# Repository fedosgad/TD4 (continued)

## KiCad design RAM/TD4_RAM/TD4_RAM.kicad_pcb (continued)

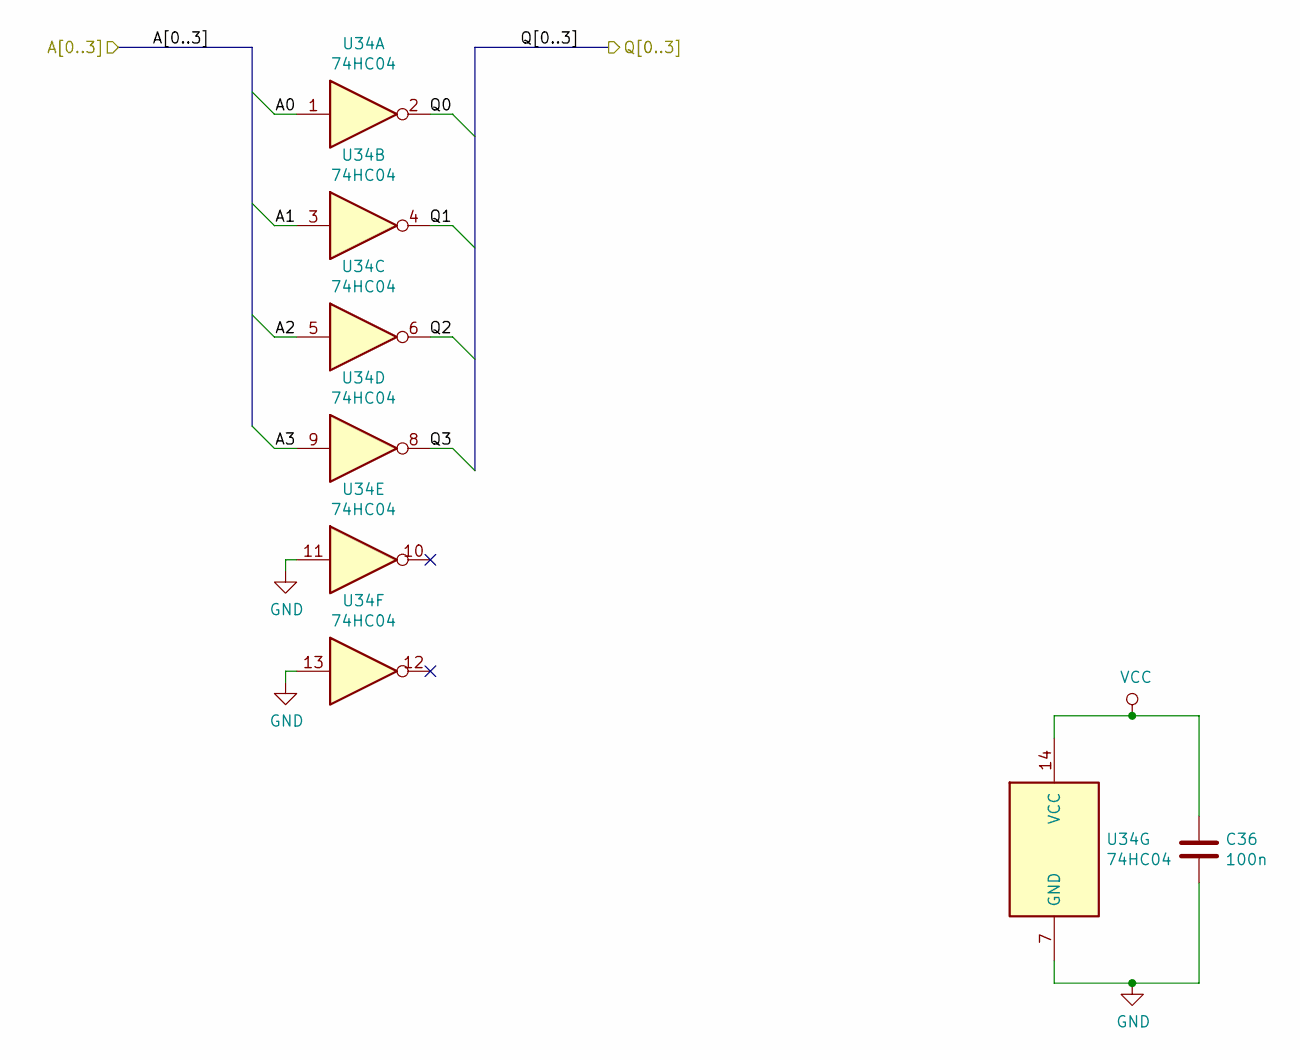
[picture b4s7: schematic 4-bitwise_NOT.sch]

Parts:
C5: 100n; C_0805_2012Metric
U3: 74HC04; SOIC-14_3.9x8.7mm_P1.27mm

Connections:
/Address comparator/2x Quad AND/A0: U3.2; also elsewhere on the board
/Address comparator/2x Quad AND/A1: U3.4; also elsewhere on the board
/Address comparator/2x Quad AND/A2: U3.6; also elsewhere on the board
/Address comparator/2x Quad AND/A3: U3.8; also elsewhere on the board
/Address comparator/4-bitwise NOT/A0: U3.1; also elsewhere on the board
/Address comparator/4-bitwise NOT/A1: U3.3; also elsewhere on the board
/Address comparator/4-bitwise NOT/A2: U3.5; also elsewhere on the board
/Address comparator/4-bitwise NOT/A3: U3.9; also elsewhere on the board
VCC: C5.1, U3.14 (VCC); also elsewhere on the board

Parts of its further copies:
C22, C23, C24, C25, C26, C27, C28, C29, C30, C31, C32, C33, C34, C35, C36: 100n; C_0805_2012Metric
U20, U21, U22, U23, U24, U25, U26, U27, U28, U29, U30, U31, U32, U33, U34: 74HC04; SOIC-14_3.9x8.7mm_P1.27mm

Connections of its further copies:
/Address comparator/2x Quad AND/B0: U20.2; also elsewhere on the board
/Address comparator/2x Quad AND/B1: U20.4; also elsewhere on the board
/Address comparator/2x Quad AND/B2: U20.6; also elsewhere on the board
/Address comparator/2x Quad AND/B3: U20.8; also elsewhere on the board
/Address comparator/sheet5CCFCFC3/A0: U20.1; also elsewhere on the board
/Address comparator/sheet5CCFCFC3/A1: U20.3; also elsewhere on the board
/Address comparator/sheet5CCFCFC3/A2: U20.5; also elsewhere on the board
/Address comparator/sheet5CCFCFC3/A3: U20.9; also elsewhere on the board
/Address comparator/sheet5CD0A991/A0: U22.1; also elsewhere on the board
/Address comparator/sheet5CD0A991/A1: U22.3; also elsewhere on the board
/Address comparator/sheet5CD0A991/A2: U22.5; also elsewhere on the board
/Address comparator/sheet5CD0A991/A3: U22.9; also elsewhere on the board
/Address comparator/sheet5CD1F070/A0: U31.1; also elsewhere on the board
/Address comparator/sheet5CD1F070/A1: U31.3; also elsewhere on the board
/Address comparator/sheet5CD1F070/A2: U31.5; also elsewhere on the board
/Address comparator/sheet5CD1F070/A3: U31.9; also elsewhere on the board
/Address comparator/sheet5CD1F071/A0: U32.1; also elsewhere on the board
/Address comparator/sheet5CD1F071/A1: U32.3; also elsewhere on the board
/Address comparator/sheet5CD1F071/A2: U32.5; also elsewhere on the board
/Address comparator/sheet5CD1F071/A3: U32.9; also elsewhere on the board
/Address comparator/sheet5CD1F072/A0: U33.1; also elsewhere on the board
/Address comparator/sheet5CD1F072/A1: U33.3; also elsewhere on the board
/Address comparator/sheet5CD1F072/A2: U33.5; also elsewhere on the board
/Address comparator/sheet5CD1F072/A3: U33.9; also elsewhere on the board
/Address comparator/sheet5CD1F073/A0: U34.1; also elsewhere on the board
/Address comparator/sheet5CD1F073/A1: U34.3; also elsewhere on the board
/Address comparator/sheet5CD1F073/A2: U34.5; also elsewhere on the board
/Address comparator/sheet5CD1F073/A3: U34.9; also elsewhere on the board
/Address comparator/sheet5CD2F160/A0: U23.2; also elsewhere on the board
/Address comparator/sheet5CD2F160/A1: U23.4; also elsewhere on the board
/Address comparator/sheet5CD2F160/A2: U23.6; also elsewhere on the board
/Address comparator/sheet5CD2F160/A3: U23.8; also elsewhere on the board
/Address comparator/sheet5CD2F160/B0: U24.2; also elsewhere on the board
/Address comparator/sheet5CD2F160/B1: U24.4; also elsewhere on the board
/Address comparator/sheet5CD2F160/B2: U24.6; also elsewhere on the board
/Address comparator/sheet5CD2F160/B3: U24.8; also elsewhere on the board
/Address comparator/sheet5CD03CAA/A0: U21.1; also elsewhere on the board
/Address comparator/sheet5CD03CAA/A1: U21.3; also elsewhere on the board
/Address comparator/sheet5CD03CAA/A2: U21.5; also elsewhere on the board
/Address comparator/sheet5CD03CAA/A3: U21.9; also elsewhere on the board
/Address comparator/sheet5CD3CB46/A0: U27.2; also elsewhere on the board
/Address comparator/sheet5CD3CB46/A1: U27.4; also elsewhere on the board
/Address comparator/sheet5CD3CB46/A2: U27.6; also elsewhere on the board
/Address comparator/sheet5CD3CB46/A3: U27.8; also elsewhere on the board
/Address comparator/sheet5CD3CB46/B0: U28.2; also elsewhere on the board
/Address comparator/sheet5CD3CB46/B1: U28.4; also elsewhere on the board
/Address comparator/sheet5CD3CB46/B2: U28.6; also elsewhere on the board
/Address comparator/sheet5CD3CB46/B3: U28.8; also elsewhere on the board
/Address comparator/sheet5CD3CB47/A0: U29.2; also elsewhere on the board
/Address comparator/sheet5CD3CB47/A1: U29.4; also elsewhere on the board
/Address comparator/sheet5CD3CB47/A2: U29.6; also elsewhere on the board
/Address comparator/sheet5CD3CB47/A3: U29.8; also elsewhere on the board
/Address comparator/sheet5CD3CB47/B0: U30.2; also elsewhere on the board
/Address comparator/sheet5CD3CB47/B1: U30.4; also elsewhere on the board
/Address comparator/sheet5CD3CB47/B2: U30.6; also elsewhere on the board
/Address comparator/sheet5CD3CB47/B3: U30.8; also elsewhere on the board
/Address comparator/sheet5CD3CB48/A0: U31.2; also elsewhere on the board
/Address comparator/sheet5CD3CB48/A1: U31.4; also elsewhere on the board
/Address comparator/sheet5CD3CB48/A2: U31.6; also elsewhere on the board
/Address comparator/sheet5CD3CB48/A3: U31.8; also elsewhere on the board
/Address comparator/sheet5CD3CB48/B0: U32.2; also elsewhere on the board
/Address comparator/sheet5CD3CB48/B1: U32.4; also elsewhere on the board
/Address comparator/sheet5CD3CB48/B2: U32.6; also elsewhere on the board
/Address comparator/sheet5CD3CB48/B3: U32.8; also elsewhere on the board
/Address comparator/sheet5CD3CB49/A0: U33.2; also elsewhere on the board
/Address comparator/sheet5CD3CB49/A1: U33.4; also elsewhere on the board
/Address comparator/sheet5CD3CB49/A2: U33.6; also elsewhere on the board
/Address comparator/sheet5CD3CB49/A3: U33.8; also elsewhere on the board
/Address comparator/sheet5CD3CB49/B0: U34.2; also elsewhere on the board
/Address comparator/sheet5CD3CB49/B1: U34.4; also elsewhere on the board
/Address comparator/sheet5CD3CB49/B2: U34.6; also elsewhere on the board
/Address comparator/sheet5CD3CB49/B3: U34.8; also elsewhere on the board
/Address comparator/sheet5CD35E49/A0: U25.2; also elsewhere on the board
/Address comparator/sheet5CD35E49/A1: U25.4; also elsewhere on the board
/Address comparator/sheet5CD35E49/A2: U25.6; also elsewhere on the board
/Address comparator/sheet5CD35E49/A3: U25.8; also elsewhere on the board
/Address comparator/sheet5CD35E49/B0: U26.2; also elsewhere on the board
/Address comparator/sheet5CD35E49/B1: U26.4; also elsewhere on the board
/Address comparator/sheet5CD35E49/B2: U26.6; also elsewhere on the board
/Address comparator/sheet5CD35E49/B3: U26.8; also elsewhere on the board
/Address comparator/sheet5CD1837A/A0: U27.1; also elsewhere on the board
/Address comparator/sheet5CD1837A/A1: U27.3; also elsewhere on the board
/Address comparator/sheet5CD1837A/A2: U27.5; also elsewhere on the board
/Address comparator/sheet5CD1837A/A3: U27.9; also elsewhere on the board
/Address comparator/sheet5CD1837B/A0: U28.1; also elsewhere on the board
/Address comparator/sheet5CD1837B/A1: U28.3; also elsewhere on the board
/Address comparator/sheet5CD1837B/A2: U28.5; also elsewhere on the board
/Address comparator/sheet5CD1837B/A3: U28.9; also elsewhere on the board
/Address comparator/sheet5CD1837C/A0: U29.1; also elsewhere on the board
/Address comparator/sheet5CD1837C/A1: U29.3; also elsewhere on the board
/Address comparator/sheet5CD1837C/A2: U29.5; also elsewhere on the board
/Address comparator/sheet5CD1837C/A3: U29.9; also elsewhere on the board
/Address comparator/sheet5CD1837D/A0: U30.1; also elsewhere on the board
/Address comparator/sheet5CD1837D/A1: U30.3; also elsewhere on the board
/Address comparator/sheet5CD1837D/A2: U30.5; also elsewhere on the board
/Address comparator/sheet5CD1837D/A3: U30.9; also elsewhere on the board
/Address comparator/sheet5CD11684/A0: U23.1; also elsewhere on the board
/Address comparator/sheet5CD11684/A1: U23.3; also elsewhere on the board
/Address comparator/sheet5CD11684/A2: U23.5; also elsewhere on the board
/Address comparator/sheet5CD11684/A3: U23.9; also elsewhere on the board
/Address comparator/sheet5CD11685/A0: U24.1; also elsewhere on the board
/Address comparator/sheet5CD11685/A1: U24.3; also elsewhere on the board
/Address comparator/sheet5CD11685/A2: U24.5; also elsewhere on the board
/Address comparator/sheet5CD11685/A3: U24.9; also elsewhere on the board
/Address comparator/sheet5CD11686/A0: U25.1; also elsewhere on the board
/Address comparator/sheet5CD11686/A1: U25.3; also elsewhere on the board
/Address comparator/sheet5CD11686/A2: U25.5; also elsewhere on the board
/Address comparator/sheet5CD11686/A3: U25.9; also elsewhere on the board
/Address comparator/sheet5CD11687/A0: U26.1; also elsewhere on the board
/Address comparator/sheet5CD11687/A1: U26.3; also elsewhere on the board
/Address comparator/sheet5CD11687/A2: U26.5; also elsewhere on the board
/Address comparator/sheet5CD11687/A3: U26.9; also elsewhere on the board
/Address comparator/sheet5CD28477/A0: U21.2; also elsewhere on the board
/Address comparator/sheet5CD28477/A1: U21.4; also elsewhere on the board
/Address comparator/sheet5CD28477/A2: U21.6; also elsewhere on the board
/Address comparator/sheet5CD28477/A3: U21.8; also elsewhere on the board
/Address comparator/sheet5CD28477/B0: U22.2; also elsewhere on the board
/Address comparator/sheet5CD28477/B1: U22.4; also elsewhere on the board
/Address comparator/sheet5CD28477/B2: U22.6; also elsewhere on the board
/Address comparator/sheet5CD28477/B3: U22.8; also elsewhere on the board
VCC: C22.1, C23.1, C24.1, C25.1, C26.1, C27.1, C28.1, C29.1, C30.1, C31.1, C32.1, C33.1, C34.1, C35.1, C36.1, U20.14 (VCC), U21.14 (VCC), U22.14 (VCC), U23.14 (VCC), U24.14 (VCC), U25.14 (VCC), U26.14 (VCC), U27.14 (VCC), U28.14 (VCC), U29.14 (VCC), U30.14 (VCC), U31.14 (VCC), U32.14 (VCC), U33.14 (VCC), U34.14 (VCC); also elsewhere on the board

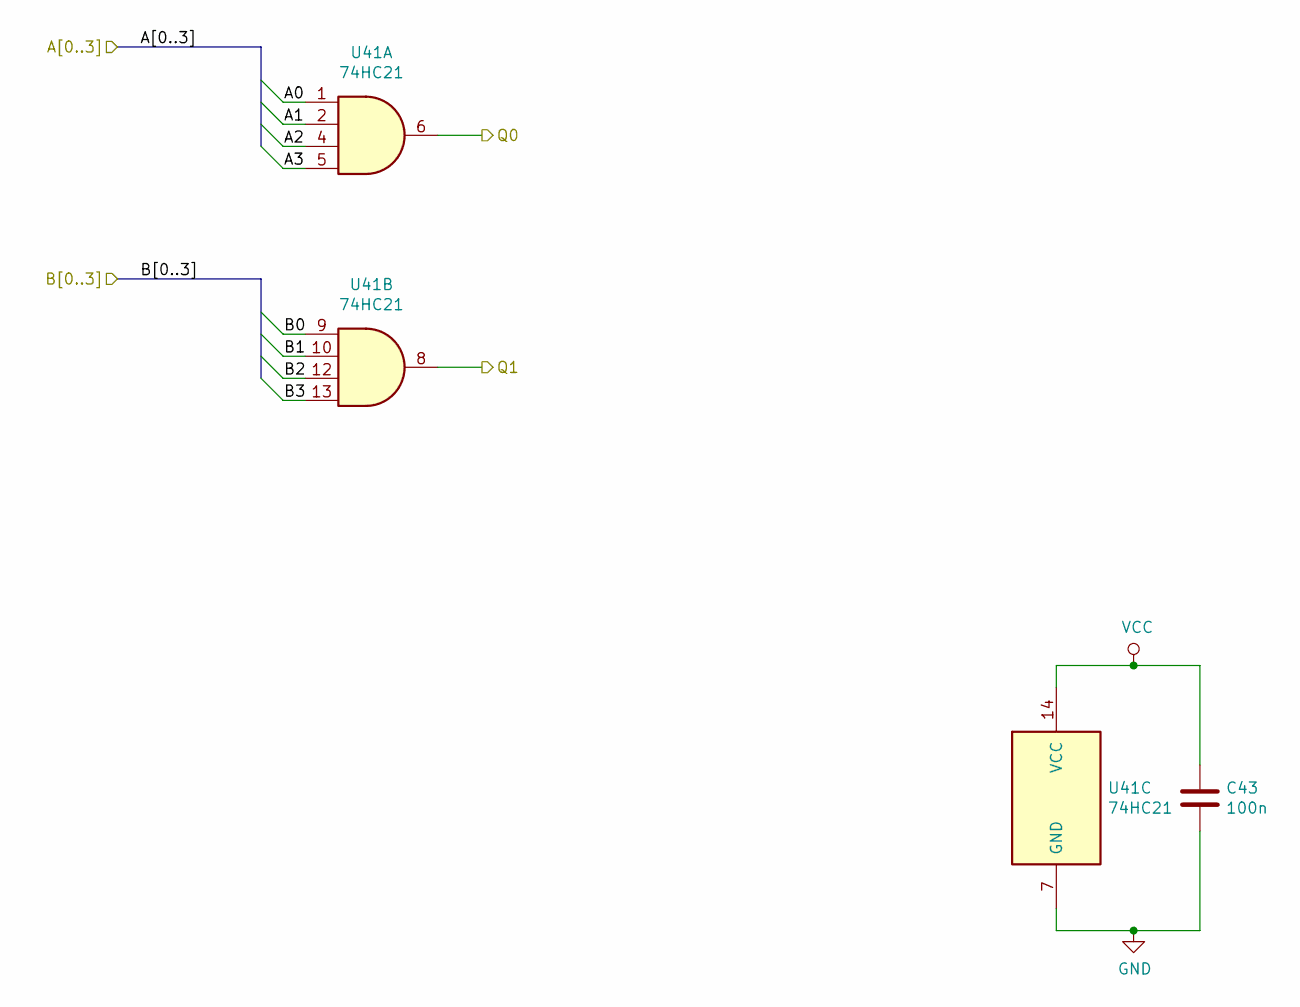
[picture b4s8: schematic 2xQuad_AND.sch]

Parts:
C6: 100n; C_0805_2012Metric
U4: 74HC21; SOIC-14_3.9x8.7mm_P1.27mm

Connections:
/Address comparator/2x Quad AND/A0: U4.1; also elsewhere on the board
/Address comparator/2x Quad AND/A1: U4.2; also elsewhere on the board
/Address comparator/2x Quad AND/A2: U4.4; also elsewhere on the board
/Address comparator/2x Quad AND/A3: U4.5; also elsewhere on the board
/Address comparator/2x Quad AND/B0: U4.9; also elsewhere on the board
/Address comparator/2x Quad AND/B1: U4.10; also elsewhere on the board
/Address comparator/2x Quad AND/B2: U4.12; also elsewhere on the board
/Address comparator/2x Quad AND/B3: U4.13; also elsewhere on the board
/sheet5CBF05D3/B0: U4.6; also elsewhere on the board
/sheet5CBF05D3/B1: U4.8; also elsewhere on the board
VCC: C6.1, U4.14 (VCC); also elsewhere on the board

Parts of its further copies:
C37, C38, C39, C40, C41, C42, C43: 100n; C_0805_2012Metric
U35, U36, U37, U38, U39, U40, U41: 74HC21; SOIC-14_3.9x8.7mm_P1.27mm

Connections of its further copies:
/Address comparator/sheet5CD2F160/A0: U36.1; also elsewhere on the board
/Address comparator/sheet5CD2F160/A1: U36.2; also elsewhere on the board
/Address comparator/sheet5CD2F160/A2: U36.4; also elsewhere on the board
/Address comparator/sheet5CD2F160/A3: U36.5; also elsewhere on the board
/Address comparator/sheet5CD2F160/B0: U36.9; also elsewhere on the board
/Address comparator/sheet5CD2F160/B1: U36.10; also elsewhere on the board
/Address comparator/sheet5CD2F160/B2: U36.12; also elsewhere on the board
/Address comparator/sheet5CD2F160/B3: U36.13; also elsewhere on the board
/Address comparator/sheet5CD3CB46/A0: U38.1; also elsewhere on the board
/Address comparator/sheet5CD3CB46/A1: U38.2; also elsewhere on the board
/Address comparator/sheet5CD3CB46/A2: U38.4; also elsewhere on the board
/Address comparator/sheet5CD3CB46/A3: U38.5; also elsewhere on the board
/Address comparator/sheet5CD3CB46/B0: U38.9; also elsewhere on the board
/Address comparator/sheet5CD3CB46/B1: U38.10; also elsewhere on the board
/Address comparator/sheet5CD3CB46/B2: U38.12; also elsewhere on the board
/Address comparator/sheet5CD3CB46/B3: U38.13; also elsewhere on the board
/Address comparator/sheet5CD3CB47/A0: U39.1; also elsewhere on the board
/Address comparator/sheet5CD3CB47/A1: U39.2; also elsewhere on the board
/Address comparator/sheet5CD3CB47/A2: U39.4; also elsewhere on the board
/Address comparator/sheet5CD3CB47/A3: U39.5; also elsewhere on the board
/Address comparator/sheet5CD3CB47/B0: U39.9; also elsewhere on the board
/Address comparator/sheet5CD3CB47/B1: U39.10; also elsewhere on the board
/Address comparator/sheet5CD3CB47/B2: U39.12; also elsewhere on the board
/Address comparator/sheet5CD3CB47/B3: U39.13; also elsewhere on the board
/Address comparator/sheet5CD3CB48/A0: U40.1; also elsewhere on the board
/Address comparator/sheet5CD3CB48/A1: U40.2; also elsewhere on the board
/Address comparator/sheet5CD3CB48/A2: U40.4; also elsewhere on the board
/Address comparator/sheet5CD3CB48/A3: U40.5; also elsewhere on the board
/Address comparator/sheet5CD3CB48/B0: U40.9; also elsewhere on the board
/Address comparator/sheet5CD3CB48/B1: U40.10; also elsewhere on the board
/Address comparator/sheet5CD3CB48/B2: U40.12; also elsewhere on the board
/Address comparator/sheet5CD3CB48/B3: U40.13; also elsewhere on the board
/Address comparator/sheet5CD3CB49/A0: U41.1; also elsewhere on the board
/Address comparator/sheet5CD3CB49/A1: U41.2; also elsewhere on the board
/Address comparator/sheet5CD3CB49/A2: U41.4; also elsewhere on the board
/Address comparator/sheet5CD3CB49/A3: U41.5; also elsewhere on the board
/Address comparator/sheet5CD3CB49/B0: U41.9; also elsewhere on the board
/Address comparator/sheet5CD3CB49/B1: U41.10; also elsewhere on the board
/Address comparator/sheet5CD3CB49/B2: U41.12; also elsewhere on the board
/Address comparator/sheet5CD3CB49/B3: U41.13; also elsewhere on the board
/Address comparator/sheet5CD35E49/A0: U37.1; also elsewhere on the board
/Address comparator/sheet5CD35E49/A1: U37.2; also elsewhere on the board
/Address comparator/sheet5CD35E49/A2: U37.4; also elsewhere on the board
/Address comparator/sheet5CD35E49/A3: U37.5; also elsewhere on the board
/Address comparator/sheet5CD35E49/B0: U37.9; also elsewhere on the board
/Address comparator/sheet5CD35E49/B1: U37.10; also elsewhere on the board
/Address comparator/sheet5CD35E49/B2: U37.12; also elsewhere on the board
/Address comparator/sheet5CD35E49/B3: U37.13; also elsewhere on the board
/Address comparator/sheet5CD28477/A0: U35.1; also elsewhere on the board
/Address comparator/sheet5CD28477/A1: U35.2; also elsewhere on the board
/Address comparator/sheet5CD28477/A2: U35.4; also elsewhere on the board
/Address comparator/sheet5CD28477/A3: U35.5; also elsewhere on the board
/Address comparator/sheet5CD28477/B0: U35.9; also elsewhere on the board
/Address comparator/sheet5CD28477/B1: U35.10; also elsewhere on the board
/Address comparator/sheet5CD28477/B2: U35.12; also elsewhere on the board
/Address comparator/sheet5CD28477/B3: U35.13; also elsewhere on the board
/sheet5CBF05D3/B2: U35.6; also elsewhere on the board
/sheet5CBF05D3/B3: U35.8; also elsewhere on the board
/sheet5CBF05D3/B4: U36.6; also elsewhere on the board
/sheet5CBF05D3/B5: U36.8; also elsewhere on the board
/sheet5CBF05D3/B6: U37.6; also elsewhere on the board
/sheet5CBF05D3/B7: U37.8; also elsewhere on the board
/sheet5CBF05D3/B8: U38.6; also elsewhere on the board
/sheet5CBF05D3/B9: U38.8; also elsewhere on the board
/sheet5CBF05D3/B10: U39.6; also elsewhere on the board
/sheet5CBF05D3/B11: U39.8; also elsewhere on the board
/sheet5CBF05D3/B12: U40.6; also elsewhere on the board
/sheet5CBF05D3/B13: U40.8; also elsewhere on the board
/sheet5CBF05D3/B14: U41.6; also elsewhere on the board
/sheet5CBF05D3/B15: U41.8; also elsewhere on the board
VCC: C37.1, C38.1, C39.1, C40.1, C41.1, C42.1, C43.1, U35.14 (VCC), U36.14 (VCC), U37.14 (VCC), U38.14 (VCC), U39.14 (VCC), U40.14 (VCC), U41.14 (VCC); also elsewhere on the board

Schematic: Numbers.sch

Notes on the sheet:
0 4 8 C 1 5 9 D 2 6 A E 3 7 B F

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
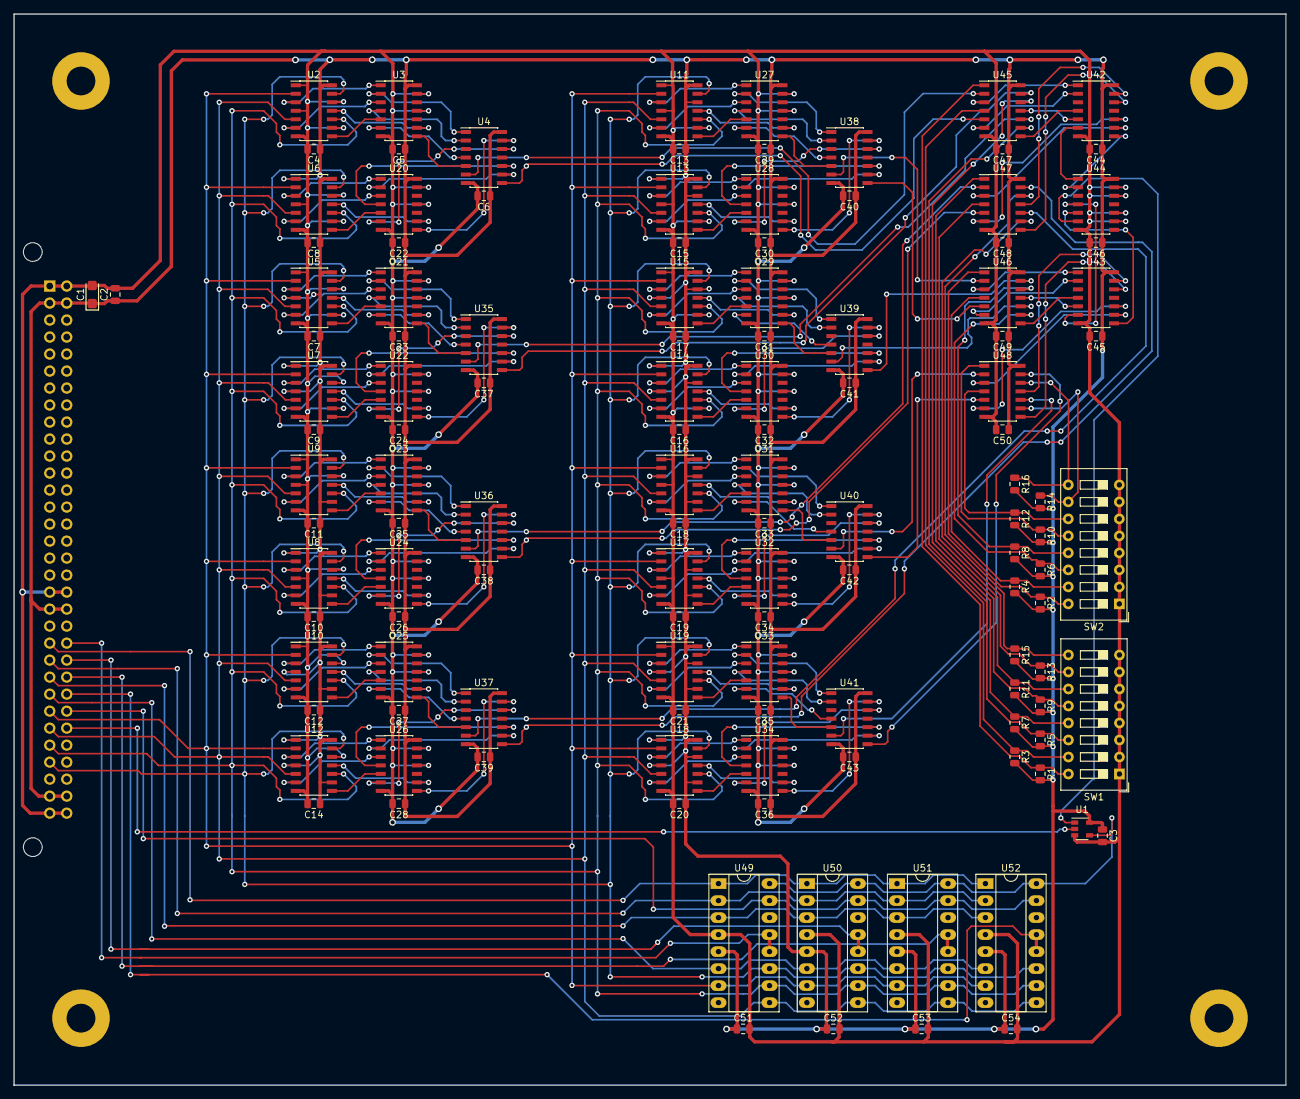
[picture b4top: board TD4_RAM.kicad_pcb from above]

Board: 2 copper layers, 190.0 x 160.0 mm, 125 parts (1 on the bottom side), 198 nets.

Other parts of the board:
C2, C3: 100n; C_0805_2012Metric

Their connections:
VCC: C2.1, C3.1; also elsewhere on the board

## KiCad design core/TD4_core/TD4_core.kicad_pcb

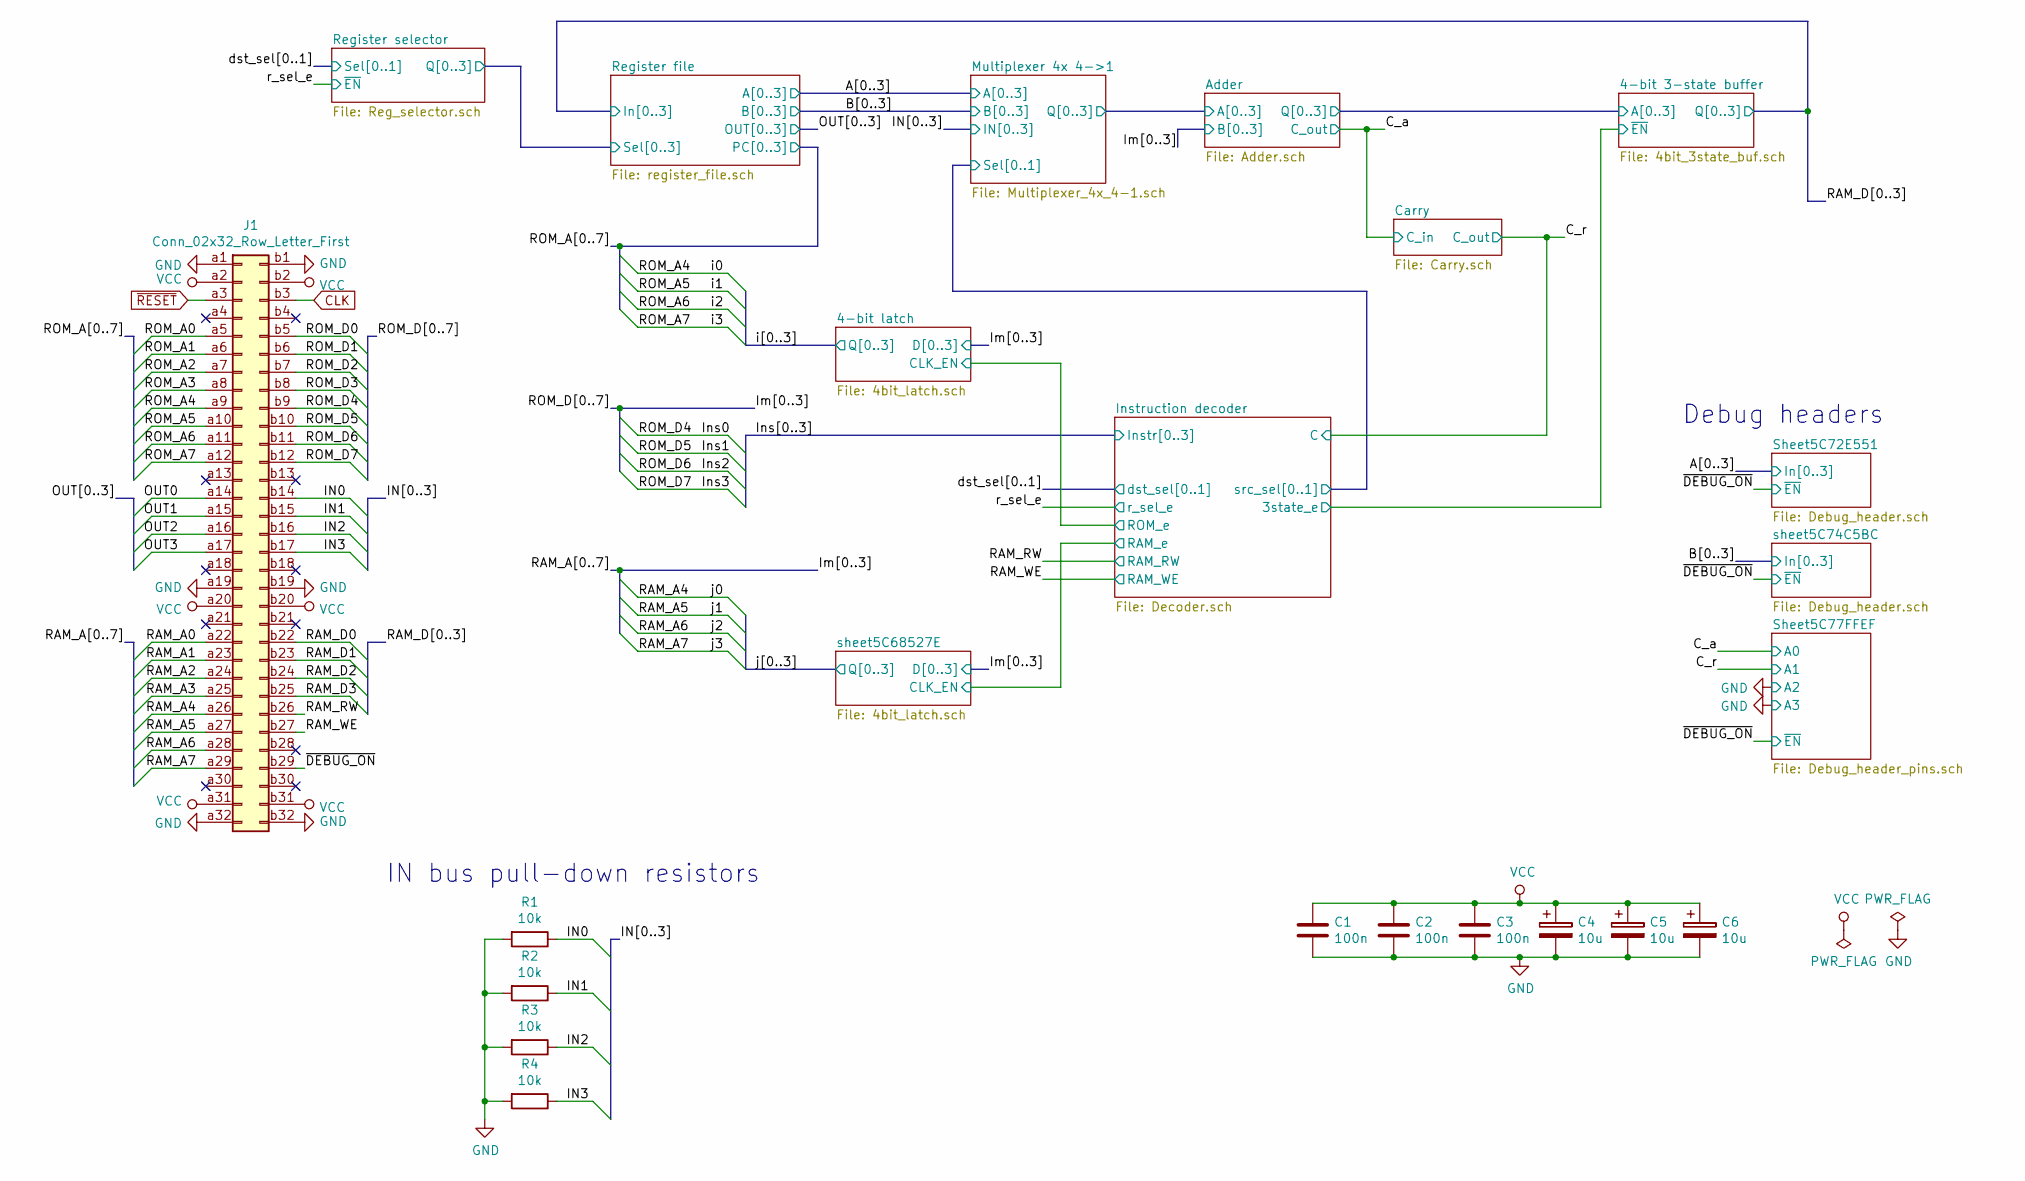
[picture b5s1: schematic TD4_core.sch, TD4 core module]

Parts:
C1, C2, C3: 100n; C_0805_2012Metric
C4, C5, C6: 10u; CP_EIA-3216-18_Kemet-A
J1: Conn_02x32_Row_Letter_First; DIN41612_B_2x32_Horizontal
R1, R2, R3, R4: 10k; R_0805_2012Metric

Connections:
/IN0: J1.b14, R1.1; also elsewhere on the board
/IN1: J1.b15, R2.1; also elsewhere on the board
/IN2: J1.b16, R3.1; also elsewhere on the board
/IN3: J1.b17, R4.1; also elsewhere on the board
/Ins0: J1.b9; also elsewhere on the board
/Ins1: J1.b10; also elsewhere on the board
/Ins2: J1.b11; also elsewhere on the board
/Ins3: J1.b12; also elsewhere on the board
/OUT0: J1.a14; also elsewhere on the board
/OUT1: J1.a15; also elsewhere on the board
/OUT2: J1.a16; also elsewhere on the board
/OUT3: J1.a17; also elsewhere on the board
/RAM_A4: J1.a26; also elsewhere on the board
/RAM_A5: J1.a27; also elsewhere on the board
/RAM_A6: J1.a28; also elsewhere on the board
/RAM_A7: J1.a29; also elsewhere on the board
/RAM_D0: J1.b22; also elsewhere on the board
/RAM_D1: J1.b23; also elsewhere on the board
/RAM_D2: J1.b24; also elsewhere on the board
/RAM_D3: J1.b25; also elsewhere on the board
/RAM_RW: J1.b26; also elsewhere on the board
/RAM_WE: J1.b27; also elsewhere on the board
/ROM_A0: J1.a5; also elsewhere on the board
/ROM_A1: J1.a6; also elsewhere on the board
/ROM_A2: J1.a7; also elsewhere on the board
/ROM_A3: J1.a8; also elsewhere on the board
/ROM_A4: J1.a9; also elsewhere on the board
/ROM_A5: J1.a10; also elsewhere on the board
/ROM_A6: J1.a11; also elsewhere on the board
/ROM_A7: J1.a12; also elsewhere on the board
/~DEBUG_ON~: J1.b29; also elsewhere on the board
CLK: J1.b3; also elsewhere on the board
~RESET: J1.a3; also elsewhere on the board

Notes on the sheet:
Debug headers
IN bus pull-down resistors

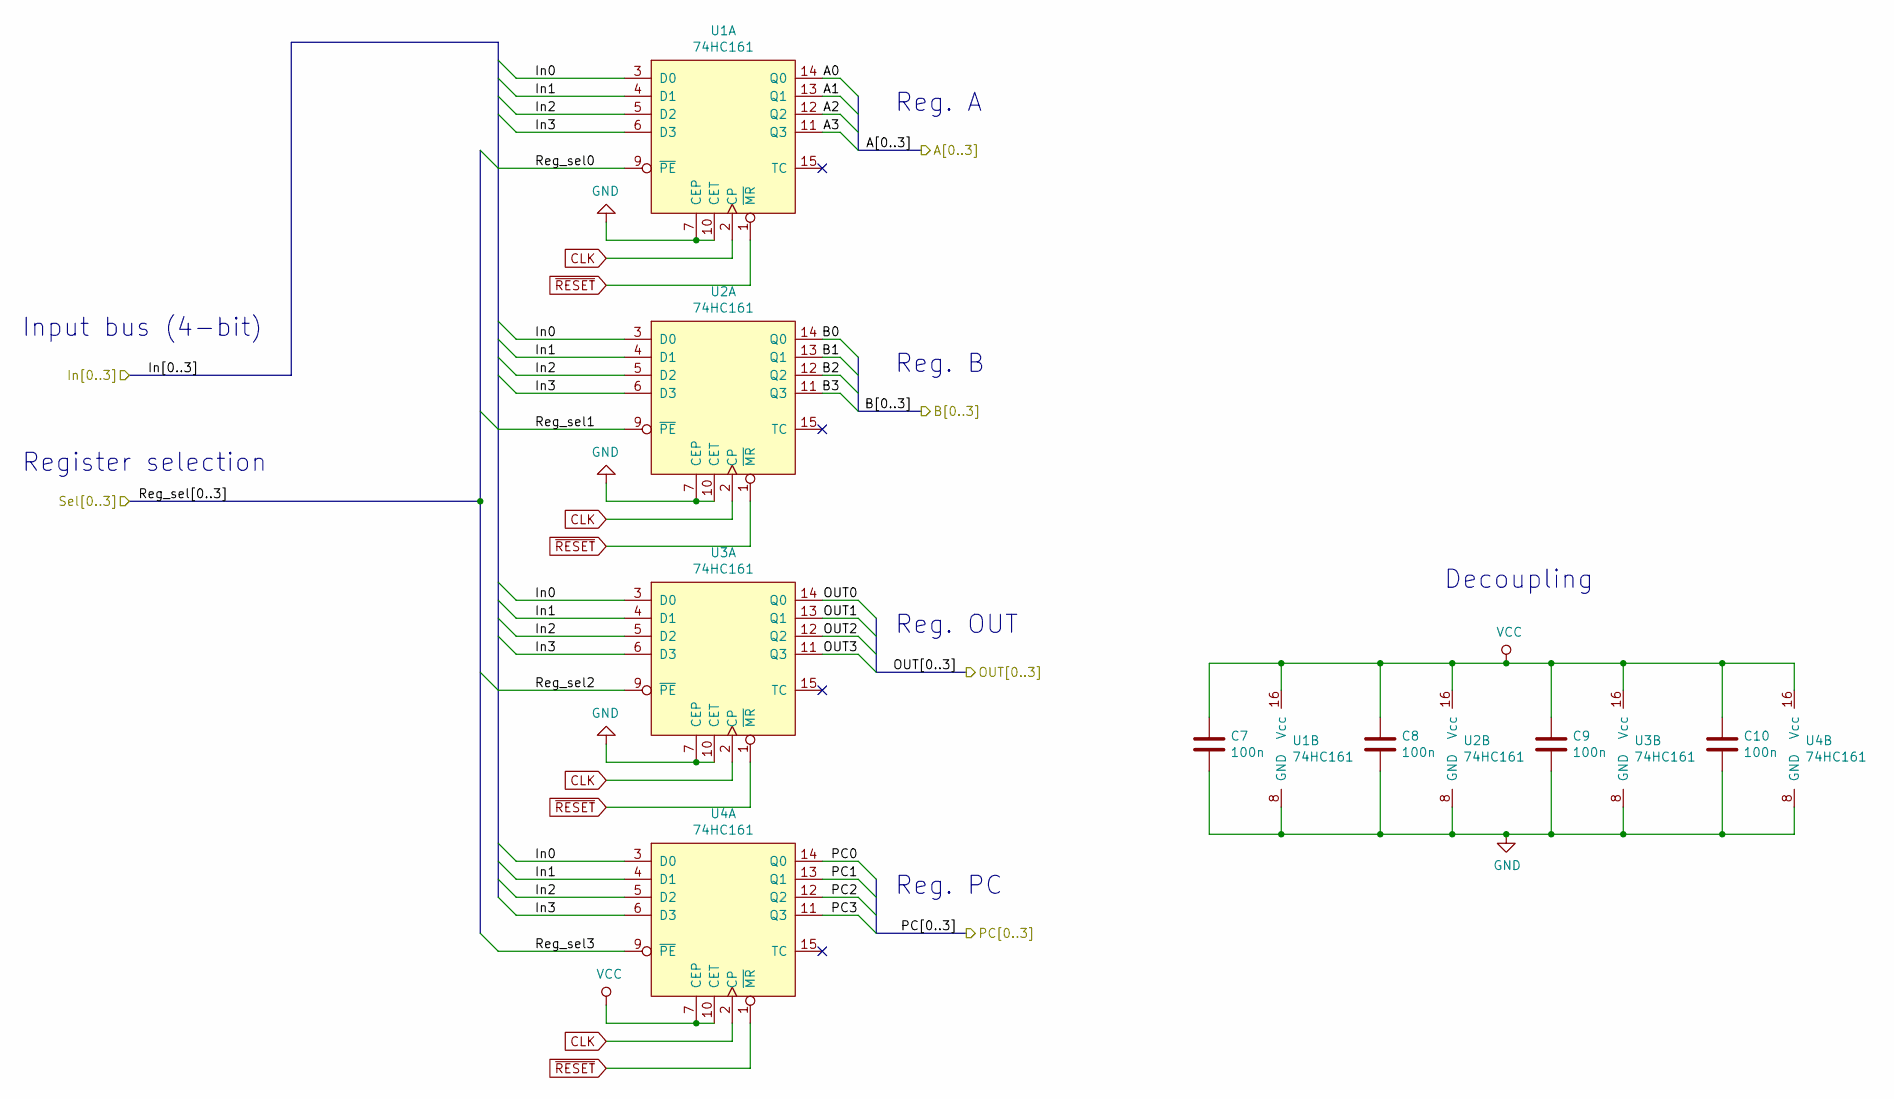
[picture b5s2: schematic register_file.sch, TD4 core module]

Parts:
C7, C8, C9, C10: 100n; C_0805_2012Metric
U1, U2, U3, U4: 74HC161; SOIC-16_3.9x9.9mm_P1.27mm

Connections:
/Multiplexer 4x 4->1/A0: U1.14 (Q0); also elsewhere on the board
/Multiplexer 4x 4->1/A1: U1.13 (Q1); also elsewhere on the board
/Multiplexer 4x 4->1/A2: U1.12 (Q2); also elsewhere on the board
/Multiplexer 4x 4->1/A3: U1.11 (Q3); also elsewhere on the board
/Multiplexer 4x 4->1/B0: U2.14 (Q0); also elsewhere on the board
/Multiplexer 4x 4->1/B1: U2.13 (Q1); also elsewhere on the board
/Multiplexer 4x 4->1/B2: U2.12 (Q2); also elsewhere on the board
/Multiplexer 4x 4->1/B3: U2.11 (Q3); also elsewhere on the board
/OUT0: U3.14 (Q0); also elsewhere on the board
/OUT1: U3.13 (Q1); also elsewhere on the board
/OUT2: U3.12 (Q2); also elsewhere on the board
/OUT3: U3.11 (Q3); also elsewhere on the board
/RAM_D0: U1.3 (D0), U2.3 (D0), U3.3 (D0), U4.3 (D0); also elsewhere on the board
/RAM_D1: U1.4 (D1), U2.4 (D1), U3.4 (D1), U4.4 (D1); also elsewhere on the board
/RAM_D2: U1.5 (D2), U2.5 (D2), U3.5 (D2), U4.5 (D2); also elsewhere on the board
/RAM_D3: U1.6 (D3), U2.6 (D3), U3.6 (D3), U4.6 (D3); also elsewhere on the board
/ROM_A0: U4.14 (Q0); also elsewhere on the board
/ROM_A1: U4.13 (Q1); also elsewhere on the board
/ROM_A2: U4.12 (Q2); also elsewhere on the board
/ROM_A3: U4.11 (Q3); also elsewhere on the board
/Register selector/Q0: U1.9 (~PE); also elsewhere on the board
/Register selector/Q1: U2.9 (~PE); also elsewhere on the board
/Register selector/Q2: U3.9 (~PE); also elsewhere on the board
/Register selector/Q3: U4.9 (~PE); also elsewhere on the board
CLK: U1.2 (CP), U2.2 (CP), U3.2 (CP), U4.2 (CP); also elsewhere on the board
~RESET: U1.1 (~MR), U2.1 (~MR), U3.1 (~MR), U4.1 (~MR); also elsewhere on the board

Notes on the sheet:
Input bus (4-bit)
Reg. A
Reg. B
Reg. OUT
Reg. PC
Register selection
Decoupling
